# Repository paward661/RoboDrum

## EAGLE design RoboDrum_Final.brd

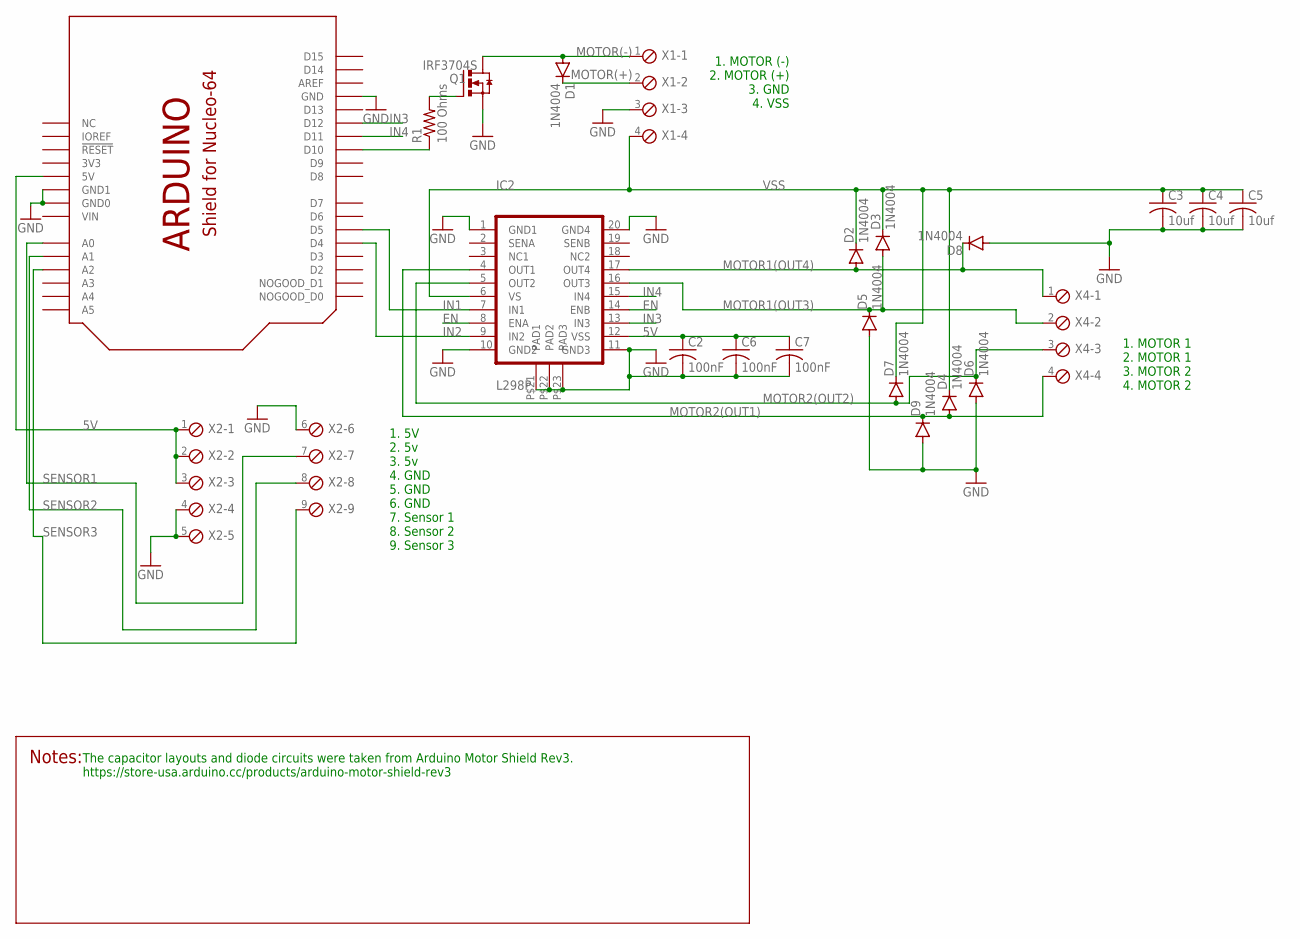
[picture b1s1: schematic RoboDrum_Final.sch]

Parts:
C2, C6, C7: 100nF; C0805
C3, C4, C5: 10uf; C1206
D1, D2, D3, D4, D5, D6, D7, D8, D9: 1N4004; DO41-10
IC2: L298P; POWER-SO20
Q1: IRF3704S; D2PACK
R1: 100 Ohms; M0805
U$1: SHIELD_FOR_NUCLE0_64_STANDARD; SHIELD_FOR_NUCLEO_64_STD
X1: SCREWTERM_4P_381; 4POL381
X2: SCREWTERM_9P_254; 9POL254
X4: SCREWTERM_4P_254; 4POL254

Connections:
3V3: U$1.3V (3V3)
5V: C2.1, C6.1, C7.1, IC2.P$12 (VSS), U$1.5V, X2.1, X2.2, X2.3
EN: IC2.P$8 (ENA), IC2.P$14 (ENB)
GND: C2.2, C3.2, C4.2, C5.2, C6.2, C7.2, D5.A, D6.A, D8.A, D9.A, IC2.P$1 (GND1), IC2.P$10 (GND2), IC2.P$11 (GND3), IC2.P$20 (GND4), IC2.P$21 (PAD1), IC2.P$22 (PAD2), IC2.P$23 (PAD3), Q1.3 (S), U$1.GND, U$1.GND1 (GND0), U$1.GND2 (GND1), X1.3, X2.4, X2.5, X2.6
IN1: IC2.P$7 (IN1), U$1.D5
IN2: IC2.P$9 (IN2), U$1.D4
IN3: IC2.P$13 (IN3), U$1.D12
IN4: IC2.P$15 (IN4), U$1.D11
MOTOR1(OUT3): D3.A, D5.C, IC2.P$16 (OUT3), X4.2
MOTOR1(OUT4): D2.A, D8.C, IC2.P$17 (OUT4), X4.1
MOTOR2(OUT1): D4.A, D9.C, IC2.P$4 (OUT1), X4.4
MOTOR2(OUT2): D6.C, D7.A, IC2.P$5 (OUT2), X4.3
MOTOR(+): D1.C, X1.2
MOTOR(-): D1.A, Q1.2 (D), X1.1
unnamed: R1.1, U$1.D10
unnamed: Q1.1 (G), R1.2
SENSOR1: U$1.A2, X2.9
SENSOR2: U$1.A1, X2.8
SENSOR3: U$1.A0, X2.7
VIN: U$1.VIN
VSS: C3.1, C4.1, C5.1, D2.C, D3.C, D4.C, D7.C, IC2.P$6 (VS), X1.4

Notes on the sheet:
1. MOTOR 1 2. MOTOR 1 3. MOTOR 2 4. MOTOR 2
1. MOTOR (-) 2. MOTOR (+) 3. GND 4. VSS
1. 5V 2. 5v 3. 5v 4. GND 5. GND 6. GND 7. Sensor 1 8. Sensor 2 9. Sensor 3
The capacitor layouts and diode circuits were taken from Arduino Motor Shield Rev3. https://store-usa.arduino.cc/products/arduino-motor-shield-rev3

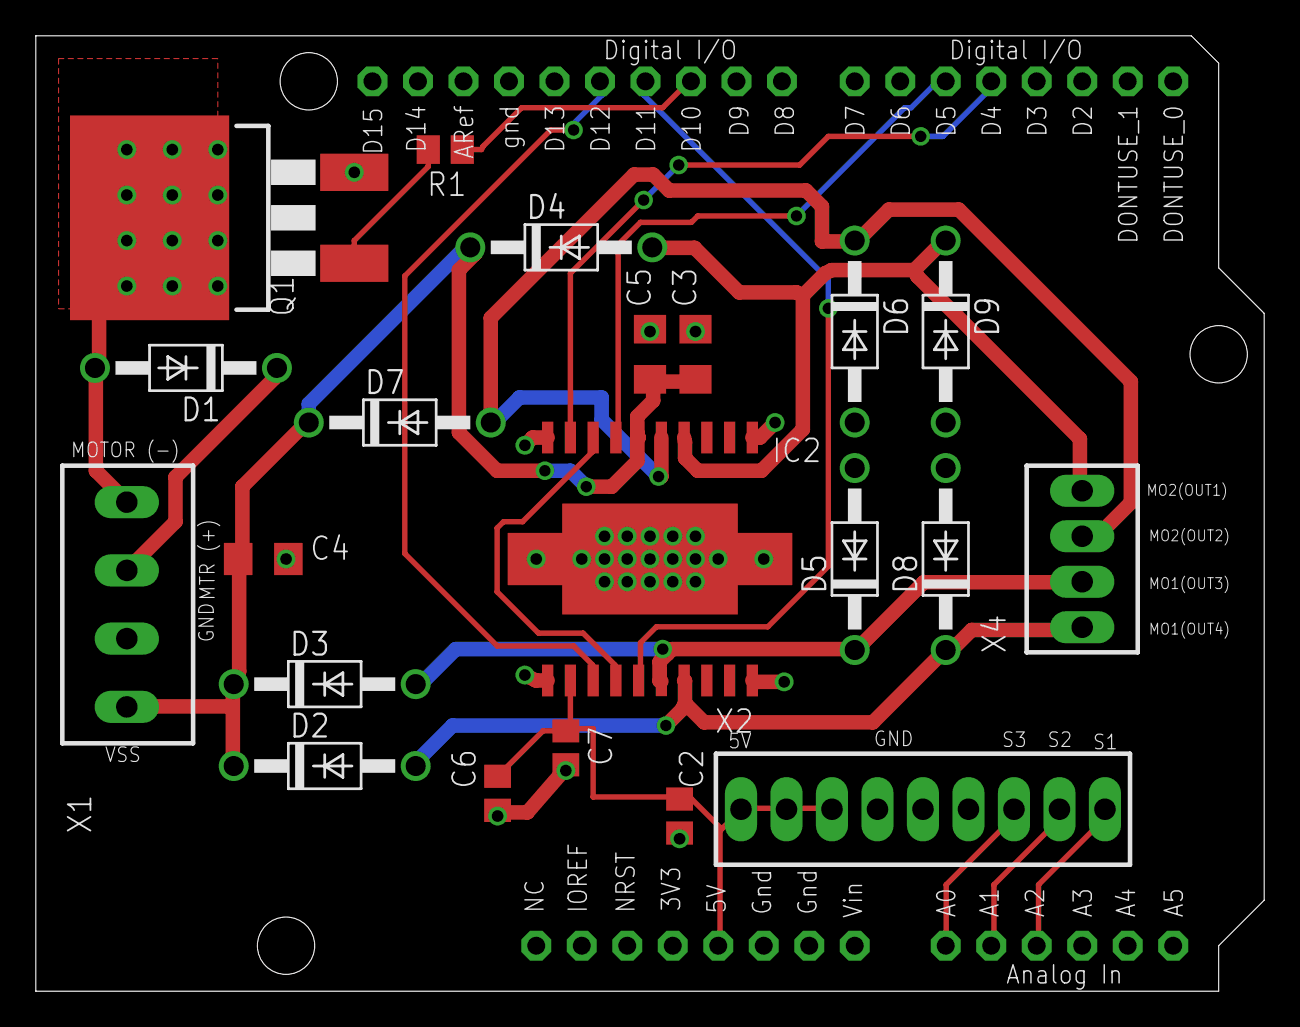
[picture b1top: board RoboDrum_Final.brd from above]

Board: 2 copper layers, 68.6 x 53.3 mm, 22 parts (0 on the bottom side), 19 nets.

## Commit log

2021-11-29 Created Main page
2021-11-29 Added the sensor_tasks file outlines still need to write the code for each task
2021-11-30 Completed the sensor driver. Has not been tested
2021-11-30 Started adding the finite state machines to the tasks
2021-12-01 Added changes to main and the sensors. Created all the motor files
2021-12-01 Fixed the timing for stop recording
2021-12-01 added shares and queues
2021-12-01 Mac edits
    edit on mac when we got the drum working
2021-12-01 Bass Drum
    Bass Drum changes
2021-12-02 Tuned
    Changed delay times and sensor thresholds
2021-12-02 tuning
2021-12-07 Crazy time stuff added
    Added time stuff to synchronize the drum timing so they dont both start at the same time. Not finished though....
2021-12-07 Reverting back to code with out code timing fixes
2021-12-08 Added some documentation and comments
2021-12-08 Fixed last code documenting and created html
2021-12-08 Eagle Files
